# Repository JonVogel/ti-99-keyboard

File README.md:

# TI-99/4A Modern Keyboard Adapter

An ESP32-S3 based adapter that lets you use a modern Bluetooth (or USB) keyboard
with a Texas Instruments TI-99/4A home computer.

The adapter installs inside the TI in place of the original keyboard connector
and emulates the original 6×8 key matrix, translating HID reports from a BLE/USB
keyboard into key presses the console's keyboard scan sees as if they came from
the original keyboard. The original keyboard can optionally run in parallel.

## Features

- **Bluetooth LE keyboard input** using the **NimBLE-Arduino** stack
  - Auto-pairing / "Just Works" bonding on first use
  - Auto-reconnect by saved address after sleep or power cycle
  - **F12** on the keyboard enters pairing mode for a new keyboard
- **Status LED** (onboard WS2812) shows connection state
- Full punctuation and symbol mapping, including the FCTN-generated characters
  (`? _ [ ] { } ' " \ | ~` `` ` `` `: < >`)
- System keys that work on real hardware: **QUIT** (Alt+=) and **CLEAR / BREAK**
  (Alt+4) to stop a running program
- Software **Alpha Lock** that fixes the original joystick-UP bug (see below)
- Optional **parallel original keyboard** — both can drive the matrix at once
- **USB keyboard input** via the native USB-OTG host port (using `EspUsbHost`),
  usable alongside or instead of BLE

## Hardware — Bill of Materials

The adapter comes in **two editions** that are electrically identical and run
the same firmware; they differ only in how the 16 level-shifter channels are
built:

- **DIY edition** (board rev ≤6): all through-hole, level shifting on four
  plug-in BOB-12009 modules — buildable with just a soldering iron.
- **Assembled edition** (board rev 7+): the shifters are 48 SMT parts
  populated by JLCPCB during fabrication. Hand work remaining: the ESP32
  (header pins on the module + two 1×22 sockets on the board, ~88 joints)
  and the connectors — real soldering, just none of the shifter fabric.

### Common parts (both editions)

| Part | Purpose |
|------|---------|
| Hosyond ESP32-S3 N16R8 dev board (USB-C, WROOM-1, 16MB flash, 8MB PSRAM) — sold in 3-packs on Amazon | MCU with USB host and BLE |
| 2× 1×22 female socket strips, 2.54mm | Sockets the ESP32 dev board (never solder the module directly) |
| 2× 1×15 male pin headers, 2.54mm (snap from 1×40 breakaway strips — e.g. Adam Tech `PH1-40-UA`, DigiKey ~$0.48/strip) | J10 (to the TI) and J20 (optional original keyboard) |
| 1×2 + 1×1 male header pins (from the same breakaway strips) | J9 bench power header, J15 spare-channel pad |
| TI PSU daisy-chain header — Molex KK-396 4-pin, `09-65-2048` (DigiKey **WM18825-ND**; alt `26-60-4040` / **WM4622-ND**) | Passes the TI's power through the board; the TI mainboard's existing female plug mates here (J14) |
| PSU-side mating plug — Molex `09-50-3041` housing (DigiKey **WM2102-ND**) + 4× `08-50-0106` crimp terminals (DigiKey **WM2300-ND**) + ~30cm of 22 AWG stranded wire | Cable from the J13 solder pads to the TI power supply's header |
| 15-pin female-to-female keyboard ribbon (DIY from bulk Dupont parts, ~$1.5–3.5/cable, no crimping — see note below; or ready-made aftermarket TI ribbon, ~$8) | Connects the adapter's male header to the TI's male keyboard header |

No voltage regulator is needed — the board runs on regulated +5V taken
straight from the TI PSU via the power daisy-chain. Crimp tool for the KK
terminals: IWISS SN-48B (~$20), or fold-and-solder the terminal barrels.

### DIY edition — additional parts (board rev ≤6)

| Part | Purpose |
|------|---------|
| PCB fabbed from `pcb/gerbers/ti99-kb-adapter_r6.zip` (2-layer, 1.6mm, HASL — ~$1/board at JLCPCB) | The carrier board, all through-hole |
| 4× BOB-12009 BSS138 level-shifter breakouts (SparkFun ~$3.50 ea, or AliExpress clones) | The 16 shifter channels (4 per module) |
| 8× 1×6 female socket strips, 2.54mm + male header pins on each BOB | Sockets the four BOB modules |

**Solder generously on the BOB headers** — under-heated joints there were the
single most common build fault. Test every finished board with
`test-matrix-loopback/` (onboard LED: green = good, red = bad).

### Assembled edition — what to order (board rev 7+)

| Item | Details |
|------|---------|
| JLCPCB order with **PCB Assembly (Economic, Top side)** using the three files in `pcb/gerbers/`: `ti99-kb-adapter_r7.zip` + `ti99-kb-adapter_BOM.csv` + `ti99-kb-adapter_CPL.csv` | Boards arrive with all 48 shifter parts (16× BSS138 `C78284`, 32× 10kΩ `C17414`) machine-soldered — ~$3/board + shipping in qty 10 |

Then add the common parts above. Still hand-soldered: the ESP32 module's
header pins, the two 1×22 board sockets, and all connectors (~120 joints) —
what assembly removes is the shifter fabric and the DIY tier's BOB/socket
work. Run `test-matrix-loopback/` after the ESP32 goes in — LED green means the
whole path (module, sockets, traces, every shifter channel) is proven in
one shot.

The adapter is intended for permanent installation inside a TI-99/4A with the
original keyboard removed (or run in parallel) and a 3D-printed cover over the
keyboard opening.

> **Sourcing the keyboard ribbon (cheap DIY):** the cable is a straight 15-way
> female-to-female run — both the adapter and the TI motherboard expose 1×15 male
> headers. Instead of a ready-made aftermarket TI ribbon (arcadeshopper, ~$8),
> build it from bulk commodity Dupont parts for ~$1.5–3.5/cable with **no
> crimping and no shells to strip**:
> - **15× female-to-female _no-shell_ pre-crimped 2.54mm leads** per cable —
>   [AliExpress](https://www.aliexpress.us/item/3256804990855815.html)
>   (search: *"Dupont 2.54mm female-to-female no-shell pre-crimped jumper wire 40P"*).
> - **2× 1×15 single-row Dupont female housings** per cable —
>   [AliExpress](https://www.aliexpress.us/item/3256806021686798.html)
>   (search: *"Dupont 2.54mm 1x15P housing female single row"*).
>
> Slide 15 bare pins into each housing — that's the whole assembly. A genuine
> Molex 1×15 housing (`50-57-9315`, DigiKey ~$1) also fits, but only accepts Molex
> crimp terminals — commodity Dupont pins won't lock in it, so stay all-Dupont.
> AliExpress links rot; the search terms are the durable fallback. Orientation
> gotcha is noted under the pinout below (red stripe = pin 15).

> **Note:** an earlier revision used TXS0108E auto-direction level shifters. They
> do **not** work for a keyboard matrix — the auto-direction detector can't
> handle open-drain / resistive loads and channels latch or oscillate. The design
> uses **BSS138 discrete MOSFET shifters**, which are bidirectional by physics and
> handle open-drain cleanly. Do not substitute TXS0108E.

## TI-99/4A Keyboard Connector Pinout

The TI's internal keyboard connector is a 1×15 single-row 0.1" header. The console
drives **six column lines** low one at a time (via a 74LS156, pulled up with 1kΩ)
and reads **eight row lines** back (into the TMS9901, pulled up with 10kΩ). The
adapter reads the columns (inputs) and drives the rows (open-drain outputs).

GPIOs below are the **v5 (straight-ribbon) mapping**: the flat ribbon lands
adapter connector (J10) pin *p* on TI pin 16−*p*, and the firmware pin map
mirrors to match. (Rev-3 boards used a 180°-twisted ribbon and a different
GPIO map — see the `v3` git tag.)

| TI pin | Signal | Matrix | ESP32 GPIO | Direction |
|:------:|--------|--------|:----------:|-----------|
| 1  | INT5  | row 2 | 13 | ESP32 → TI (drive) |
| 2  | INT6  | row 3 | 12 | ESP32 → TI (drive) |
| 3  | INT8  | row 5 | 11 | ESP32 → TI (drive) |
| 4  | INT4  | row 1 | 10 | ESP32 → TI (drive) |
| 5  | INT3  | row 0 | 9  | ESP32 → TI (drive) |
| 6  | P5    | Alpha Lock | 3 | wired, never driven (software alpha lock) |
| 7  | INT7  | row 7 | 8  | ESP32 → TI (drive) |
| 8  | 1Y1   | col 0 | 18 | TI → ESP32 (read) |
| 9  | 1Y0   | col 4 | 17 | TI → ESP32 (read) |
| 10 | INT9  | row 6 | 16 | ESP32 → TI (drive) |
| 11 | INT10 | row 4 | 15 | ESP32 → TI (drive) |
| 12 | 2Y0   | col 5 | 7  | TI → ESP32 (read) |
| 13 | 2Y1   | col 1 | 6  | TI → ESP32 (read) |
| 14 | 2Y2   | col 2 | 5  | TI → ESP32 (read) |
| 15 | 2Y3   | col 3 | 4  | TI → ESP32 (read) |

A 16th level-shifter channel (GPIO14 → **J15 "SPARE" solder pad**) is wired as a
repair path: if any matrix GPIO or shifter channel dies, jumper J15 to the dead
line's pad and remap that line's `#define` to GPIO14 — no board respin needed.

> **Ribbon orientation gotcha:** aftermarket TI keyboard ribbons mark **pin 15**
> with the red stripe, not pin 1. Verify against the silkscreen before plugging in.

### How the matrix output works

A hardware timer samples all six column inputs at ~200 kHz. Each column is
debounced asymmetrically — it becomes *active* on the first LOW sample (so the row
is driven before the ROM reads it) and only releases after two consecutive HIGH
samples (so ribbon coupling can't glitch a held key). The rows driven are the OR
of the pressed keys in every currently-active column, so an ordinary one-column
scan drives exactly that column, while the console's deliberately-overlapping QUIT
and CLEAR scans (which strobe two columns at once) are presented correctly. Rows
are open-drain, so the original keyboard can coexist on the same lines.

The dedicated Alpha Lock line (TI pin 6) is intentionally **never driven** — see
below.

## Software Build

The BLE library `BleHidHost/` lives in-tree and is picked up automatically; the
only external dependency to install is **NimBLE-Arduino**.

### Toolchain

Builds with `arduino-cli` via the included `build.bat` (Windows). FQBN:

```
esp32:esp32:esp32s3:PartitionScheme=no_ota,FlashSize=16M,PSRAM=opi
```

- `build.bat compile` — compile only
- `build.bat` — compile + upload (default COM port)
- `build.bat upload COM7` — upload to a specific port
- `build.bat monitor COM7` — serial monitor at 115200 baud

### Arduino IDE alternative

1. Install **ESP32 board support** (Boards Manager → "esp32 by Espressif")
2. Install **NimBLE-Arduino** (Library Manager → search "NimBLE-Arduino")
3. Point the sketchbook libraries at the in-tree `BleHidHost/` folder (or copy it
   into `~/Documents/Arduino/libraries/`)

### Board settings

- Board: **ESP32S3 Dev Module**
- Flash Size: **16MB**, PSRAM: **OPI PSRAM**, Partition Scheme: **no_ota**
- USB CDC On Boot: **Disabled** (frees the USB-OTG port for host mode; use the
  UART port for the serial monitor)

### Selecting input mode

At the top of `ti-99-keyboard.ino`:

```cpp
// #define INPUT_USB   // USB keyboard via USB-OTG port (currently disabled)
#define INPUT_BLE      // Bluetooth LE HID keyboard
```

## Usage

### First-time BLE pairing

1. Power on the ESP32 — the LED pulses purple (scanning)
2. Put your keyboard in pairing mode
3. The ESP32 finds the keyboard, pairs, bonds, and saves its address to NVS
4. LED turns dim green when ready; it reconnects automatically on later boots

### Re-pairing a different keyboard

Press **F12** on the currently connected keyboard. It disconnects, the ESP32
opens a 30-second pairing window (LED pulses blue), and any HID keyboard put in
pairing mode during that window is adopted as the new peer.

### LED status

| Color | Meaning |
|-------|---------|
| Pulsing blue | Startup or pairing mode |
| Pulsing purple | Scanning for keyboard |
| Steady dim green | Keyboard connected, idle |
| Bright green flash | Key pressed |
| Red blink | Error |

## Key Mapping

Modifiers pass straight through; the host **Alt** key acts as TI **FCTN**.

| Modern key | TI-99/4A |
|------------|----------|
| Alt | FCTN |
| Ctrl | CTRL |
| Shift | SHIFT |
| Caps Lock | Alpha Lock (software-emulated; see below) |

Punctuation and symbols (unshifted / shifted):

| Key | Unshifted | Shifted |
|-----|-----------|---------|
| `-` | `-` | `_` (FCTN+U) |
| `=` | `=` | `+` |
| `/` | `/` | `?` (FCTN+I) |
| `;` | `;` | `:` |
| `,` | `,` | `<` |
| `.` | `.` | `>` |
| `'` | `'` (FCTN+O) | `"` (FCTN+P) |
| `[` | `[` (FCTN+R) | `{` (FCTN+F) |
| `]` | `]` (FCTN+T) | `}` (FCTN+G) |
| `\` | `\` (FCTN+Z) | `\|` (FCTN+A) |
| `` ` `` | `` ` `` (FCTN+C) | `~` (FCTN+W) |

Editing / function keys:

| Modern key | TI-99/4A |
|------------|----------|
| Esc | FCTN+9 (BACK) |
| Backspace | FCTN+S |
| Tab | FCTN+7 |
| Delete | FCTN+1 |
| Arrows | FCTN+E / S / D / X (up / left / right / down) |
| F1–F10 | FCTN+1…0 (DEL, INS, ERASE, CLEAR, BEGIN, PROC'D, AID, REDO, BACK, …) |
| F11 | Toggle type-ahead buffer on/off |
| F12 | Enter BLE pairing mode (not forwarded to the TI) |

The F-key shortcuts let you press the standard TI FCTN+digit combos with a single
key. Two system combos worth calling out, both verified on real hardware:

- **Alt+=** → FCTN+= = **QUIT** (soft-resets to the master title screen)
- **Alt+4** (or **F4**) → FCTN+4 = **CLEAR** (breaks a running BASIC program)

### Alpha Lock and joystick compatibility

The original TI-99/4A has a notorious hardware bug: the Alpha Lock key shares an
electrical signal with joystick UP, so any game played with Alpha Lock engaged
sees a permanent UP input. The classic fix was to physically pop the Alpha Lock
key out of its socket before playing.

This adapter sidesteps the bug entirely by implementing Alpha Lock in software.
When Caps Lock is on, the adapter injects SHIFT into letter keypresses (producing
capital letters via the normal keyboard-scan path) and **never drives the
dedicated Alpha Lock line** (TI pin 6). Joysticks therefore work correctly
regardless of Caps Lock state, and numbers/punctuation are unaffected by Caps
Lock — matching the original Alpha Lock semantics.

## Status

- **BLE keyboard input:** working; tested with the RoyalAxe / ProtoArc L75.
- **TI-99/4A matrix output:** working on real hardware — typing, SHIFT/CTRL/FCTN,
  full punctuation, QUIT, and CLEAR/BREAK, with the original keyboard usable in
  parallel.
- **USB keyboard input:** working — plug a USB keyboard into the ESP32's native
  USB-OTG port (`EspUsbHost`); runs alongside BLE.

## License

MIT — see [LICENSE](LICENSE).

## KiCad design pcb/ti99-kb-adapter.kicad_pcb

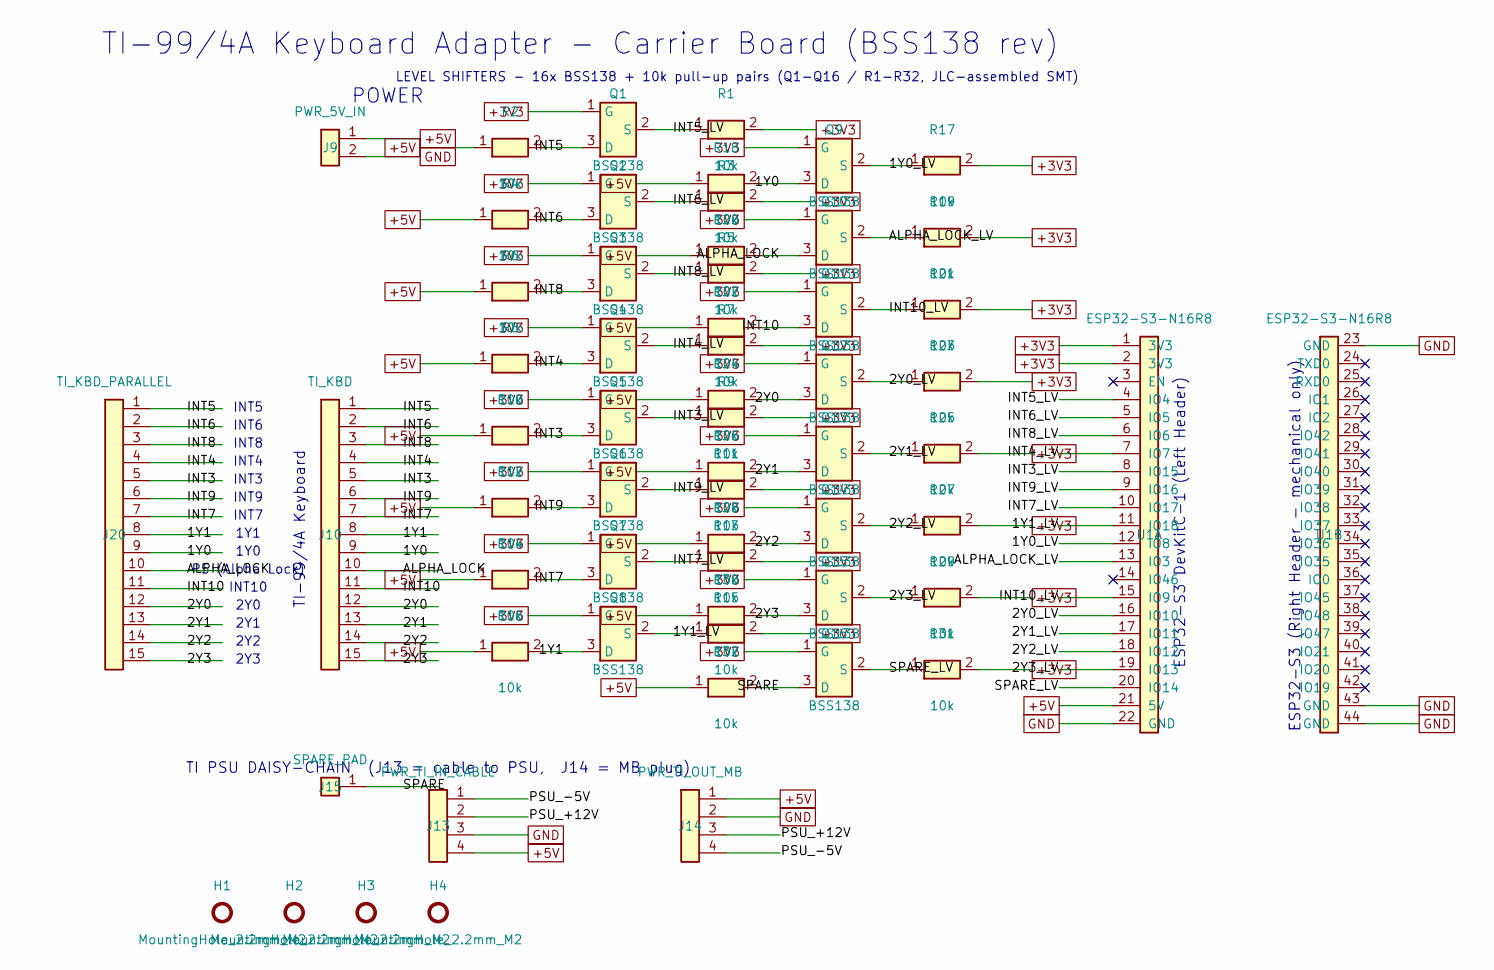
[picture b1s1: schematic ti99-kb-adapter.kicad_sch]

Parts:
H1, H2, H3, H4: MountingHole_2.2mm_M2
J9: PWR_5V_IN; PinHeader_1x02_P2.54mm_Vertical
J10: TI_KBD; PinHeader_1x15_P2.54mm_Vertical
J13: PWR_TI_IN_CABLE; J13-CableHeader-1x04
J14: PWR_TI_OUT_MB; Molex_KK-396_5273-04A_1x04_P3.96mm_Vertical
J15: SPARE_PAD; PinHeader_1x01_P2.54mm_Vertical
J20: TI_KBD_PARALLEL; PinHeader_1x15_P2.54mm_Vertical
Q1, Q2, Q3, Q4, Q5, Q6, Q7, Q8, Q9, Q10, Q11, Q12, Q13, Q14, Q15, Q16: BSS138; SOT-23; LCSC C78284
R1, R2, R3, R4, R5, R6, R7, R8, R9, R10, R11, R12, R13, R14, R15, R16, R17, R18, R19, R20, R21, R22, R23, R24, R25, R26, R27, R28, R29, R30, R31, R32: 10k; R_0805_2012Metric; LCSC C17414
U1: ESP32-S3-N16R8

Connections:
+3V3: Q1.1 (G), Q2.1 (G), Q3.1 (G), Q4.1 (G), Q5.1 (G), Q6.1 (G), Q7.1 (G), Q8.1 (G), Q9.1 (G), Q10.1 (G), Q11.1 (G), Q12.1 (G), Q13.1 (G), Q14.1 (G), Q15.1 (G), Q16.1 (G), R1.2, R3.2, R5.2, R7.2, R9.2, R11.2, R13.2, R15.2, R17.2, R19.2, R21.2, R23.2, R25.2, R27.2, R29.2, R31.2, U1.1 (3V3), U1.2 (3V3)
+5V: J9.1, J13.4, J14.1, R2.1, R4.1, R6.1, R8.1, R10.1, R12.1, R14.1, R16.1, R18.1, R20.1, R22.1, R24.1, R26.1, R28.1, R30.1, R32.1, U1.21 (5V)
/1Y0: J10.9, J20.9, Q9.3 (D), R18.2
/1Y0_LV: Q9.2 (S), R17.1, U1.12 (IO8)
/1Y1: J10.8, J20.8, Q8.3 (D), R16.2
/1Y1_LV: Q8.2 (S), R15.1, U1.11 (IO18)
/2Y0: J10.12, J20.12, Q12.3 (D), R24.2
/2Y0_LV: Q12.2 (S), R23.1, U1.16 (IO10)
/2Y1: J10.13, J20.13, Q13.3 (D), R26.2
/2Y1_LV: Q13.2 (S), R25.1, U1.17 (IO11)
/2Y2: J10.14, J20.14, Q14.3 (D), R28.2
/2Y2_LV: Q14.2 (S), R27.1, U1.18 (IO12)
/2Y3: J10.15, J20.15, Q15.3 (D), R30.2
/2Y3_LV: Q15.2 (S), R29.1, U1.19 (IO13)
/ALPHA_LOCK: J10.10, J20.10, Q10.3 (D), R20.2
/ALPHA_LOCK_LV: Q10.2 (S), R19.1, U1.13 (IO3)
/INT3: J10.5, J20.5, Q5.3 (D), R10.2
/INT3_LV: Q5.2 (S), R9.1, U1.8 (IO15)
/INT4: J10.4, J20.4, Q4.3 (D), R8.2
/INT4_LV: Q4.2 (S), R7.1, U1.7 (IO7)
/INT5: J10.1, J20.1, Q1.3 (D), R2.2
/INT5_LV: Q1.2 (S), R1.1, U1.4 (IO4)
/INT6: J10.2, J20.2, Q2.3 (D), R4.2
/INT6_LV: Q2.2 (S), R3.1, U1.5 (IO5)
/INT7: J10.7, J20.7, Q7.3 (D), R14.2
/INT7_LV: Q7.2 (S), R13.1, U1.10 (IO17)
/INT8: J10.3, J20.3, Q3.3 (D), R6.2
/INT8_LV: Q3.2 (S), R5.1, U1.6 (IO6)
/INT9: J10.6, J20.6, Q6.3 (D), R12.2
/INT9_LV: Q6.2 (S), R11.1, U1.9 (IO16)
/INT10: J10.11, J20.11, Q11.3 (D), R22.2
/INT10_LV: Q11.2 (S), R21.1, U1.15 (IO9)
/PSU_+12V: J13.2, J14.3
/PSU_-5V: J13.1, J14.4
/SPARE: J15.1 (Pin_1_1), Q16.3 (D), R32.2
/SPARE_LV: Q16.2 (S), R31.1, U1.20 (IO14)
GND: J9.2, J13.3, J14.2, U1.22 (GND), U1.23 (GND), U1.43 (GND), U1.44 (GND)

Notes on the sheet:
INT5
INT6
INT8
INT4
INT3
INT9
INT7
1Y1
1Y0
P5 (Alpha Lock)
INT10
2Y0
2Y1
2Y2
2Y3
TI-99/4A Keyboard Adapter - Carrier Board (BSS138 rev)
POWER
TI PSU DAISY-CHAIN (J13 = cable to PSU, J14 = MB plug)
LEVEL SHIFTERS - 16x BSS138 + 10k pull-up pairs (Q1-Q16 / R1-R32, JLC-assembled SMT)
ESP32-S3 DevKitC-1 (Left Header)
TI-99/4A Keyboard
ESP32-S3 (Right Header - mechanical only)

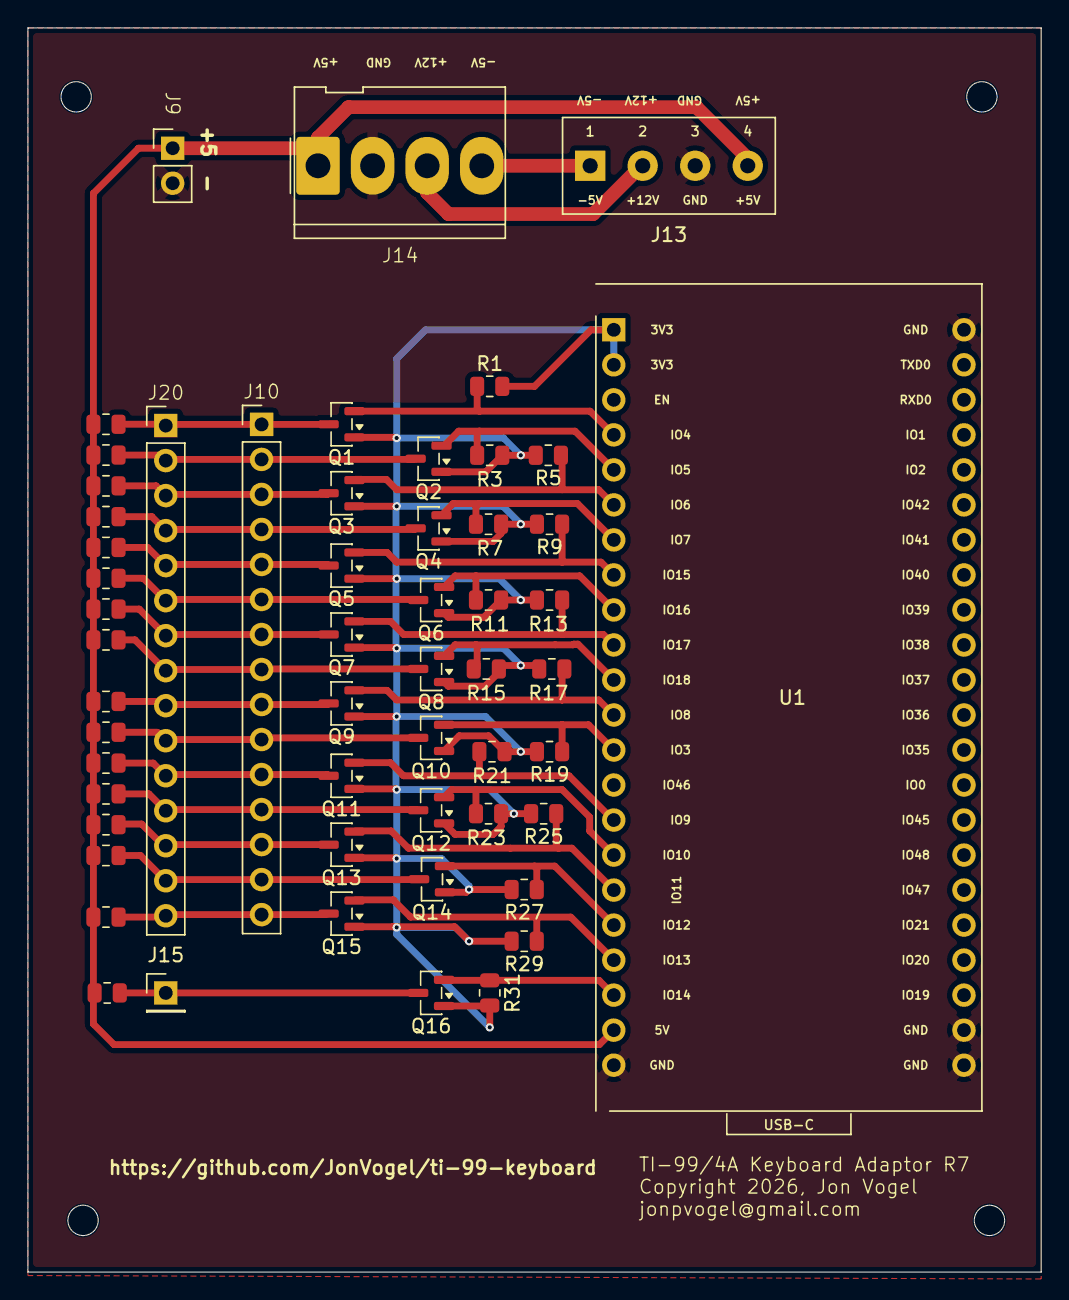
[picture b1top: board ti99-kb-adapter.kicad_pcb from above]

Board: 2 copper layers, 73.5 x 90.2 mm, 59 parts (0 on the bottom side), 37 nets.

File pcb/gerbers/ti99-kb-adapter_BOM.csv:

Comment,Designator,Footprint,LCSC
10k,"R1,R2,R3,R4,R5,R6,R7,R8,R9,R10,R11,R12,R13,R14,R15,R16,R17,R18,R19,R20,R21,R22,R23,R24,R25,R26,R27,R28,R29,R30,R31,R32",R_0805_2012Metric,C17414
BSS138,"Q1,Q2,Q3,Q4,Q5,Q6,Q7,Q8,Q9,Q10,Q11,Q12,Q13,Q14,Q15,Q16",SOT-23,C78284

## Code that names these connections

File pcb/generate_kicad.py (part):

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    j_ti2 = s.add_conn("J20", 15, 5.08, 88.90, FP_H15, "TI_KBD_PARALLEL")
    # J15: single solder pad for the SPARE repair channel. If any matrix
    # GPIO or BSS138 channel dies, jumper this pad to the dead line's
    # pad and remap that line's firmware define to PIN_SPARE.
    j_spare = s.add_conn("J15", 1, 35.56, 124.46, FP_H01, "SPARE_PAD")

    # Mounting holes (2.2mm / M2, self-tapping into the printed mount).
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    # firmware compensates for the mirror on every line (see the GPIO remap in
    # ti-99-keyboard.ino), and every J10 pin -- including alpha lock -- gets a
    # level-shifter channel and GPIO, so future re-pinning is firmware-only.
    # J10 pin 6 carries INT9 and pin 10 carries ALPHA_LOCK: through the flat
    # ribbon those land on TI-motherboard pins 10 (INT9) and 6 (alpha lock),
    # which is what puts the passive alpha-lock line where the TI expects it.

    # Signal name annotations (to the left of J_TI): the net at each J10 pin.
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    # v5 channel allocation (unchanged in V7 -- same nets, same GPIOs):
    # all 15 J10 pins have a channel (alpha lock included, GPIO3 on the
    # never-driven line where its strapping quirk is benign), plus the
    # SPARE repair channel (GPIO14 -> Q16 -> J15 solder pad). Net names
    # are J10-local; the straight ribbon lands J10 pin p on TI-mb pin
    # 16-p and firmware compensates (see remap in ti-99-keyboard.ino).
    #
    # Format: (esp_pin, j10_pin (None = SPARE pad J15), signal)
    CHANNELS = [
        (4,  1,  "INT5"),        # GPIO4  -> J10 1
        (5,  2,  "INT6"),        # GPIO5  -> J10 2
        (6,  3,  "INT8"),        # GPIO6  -> J10 3
        (7,  4,  "INT4"),        # GPIO7  -> J10 4
        (8,  5,  "INT3"),        # GPIO15 -> J10 5
        (9,  6,  "INT9"),        # GPIO16 -> J10 6
        (10, 7,  "INT7"),        # GPIO17 -> J10 7
        (11, 8,  "1Y1"),         # GPIO18 -> J10 8
        (12, 9,  "1Y0"),         # GPIO8  -> J10 9
        (13, 10, "ALPHA_LOCK"),  # GPIO3  -> J10 10
        (15, 11, "INT10"),       # GPIO9  -> J10 11
        (16, 12, "2Y0"),         # GPIO10 -> J10 12
        (17, 13, "2Y1"),         # GPIO11 -> J10 13
        (18, 14, "2Y2"),         # GPIO12 -> J10 14
        (19, 15, "2Y3"),         # GPIO13 -> J10 15
        (20, None, "SPARE"),     # GPIO14 -> J15 SPARE pad
    ]
    FP_Q = "Package_TO_SOT_SMD:SOT-23"
    FP_R = "Resistor_SMD:R_0805_2012Metric"
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    for p in [3, 14]:
        s.nc(*j_esp_l[p])

    # SPARE repair channel: GPIO14 (header pin 20) -> Q16 -> J15 solder
    # pad (the cell itself is generated in the CHANNEL CELLS loop; only
    # the pad's net label lives here). Lets any single dead channel be
    # recovered with one jumper wire + a firmware remap.
    s.pin_label(j_spare[1], "SPARE", wire_ext=10.16, label_offset=5.08)

    # Alpha lock (J10/J20 pin 10) is a full channel from GPIO3 (see
    # CHANNELS) -- no standalone passive tie. Firmware parks the GPIO as
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

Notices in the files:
pcb/ti99-kb-adapter.kicad_pcb:
Copyright 2026, Jon Vogel
